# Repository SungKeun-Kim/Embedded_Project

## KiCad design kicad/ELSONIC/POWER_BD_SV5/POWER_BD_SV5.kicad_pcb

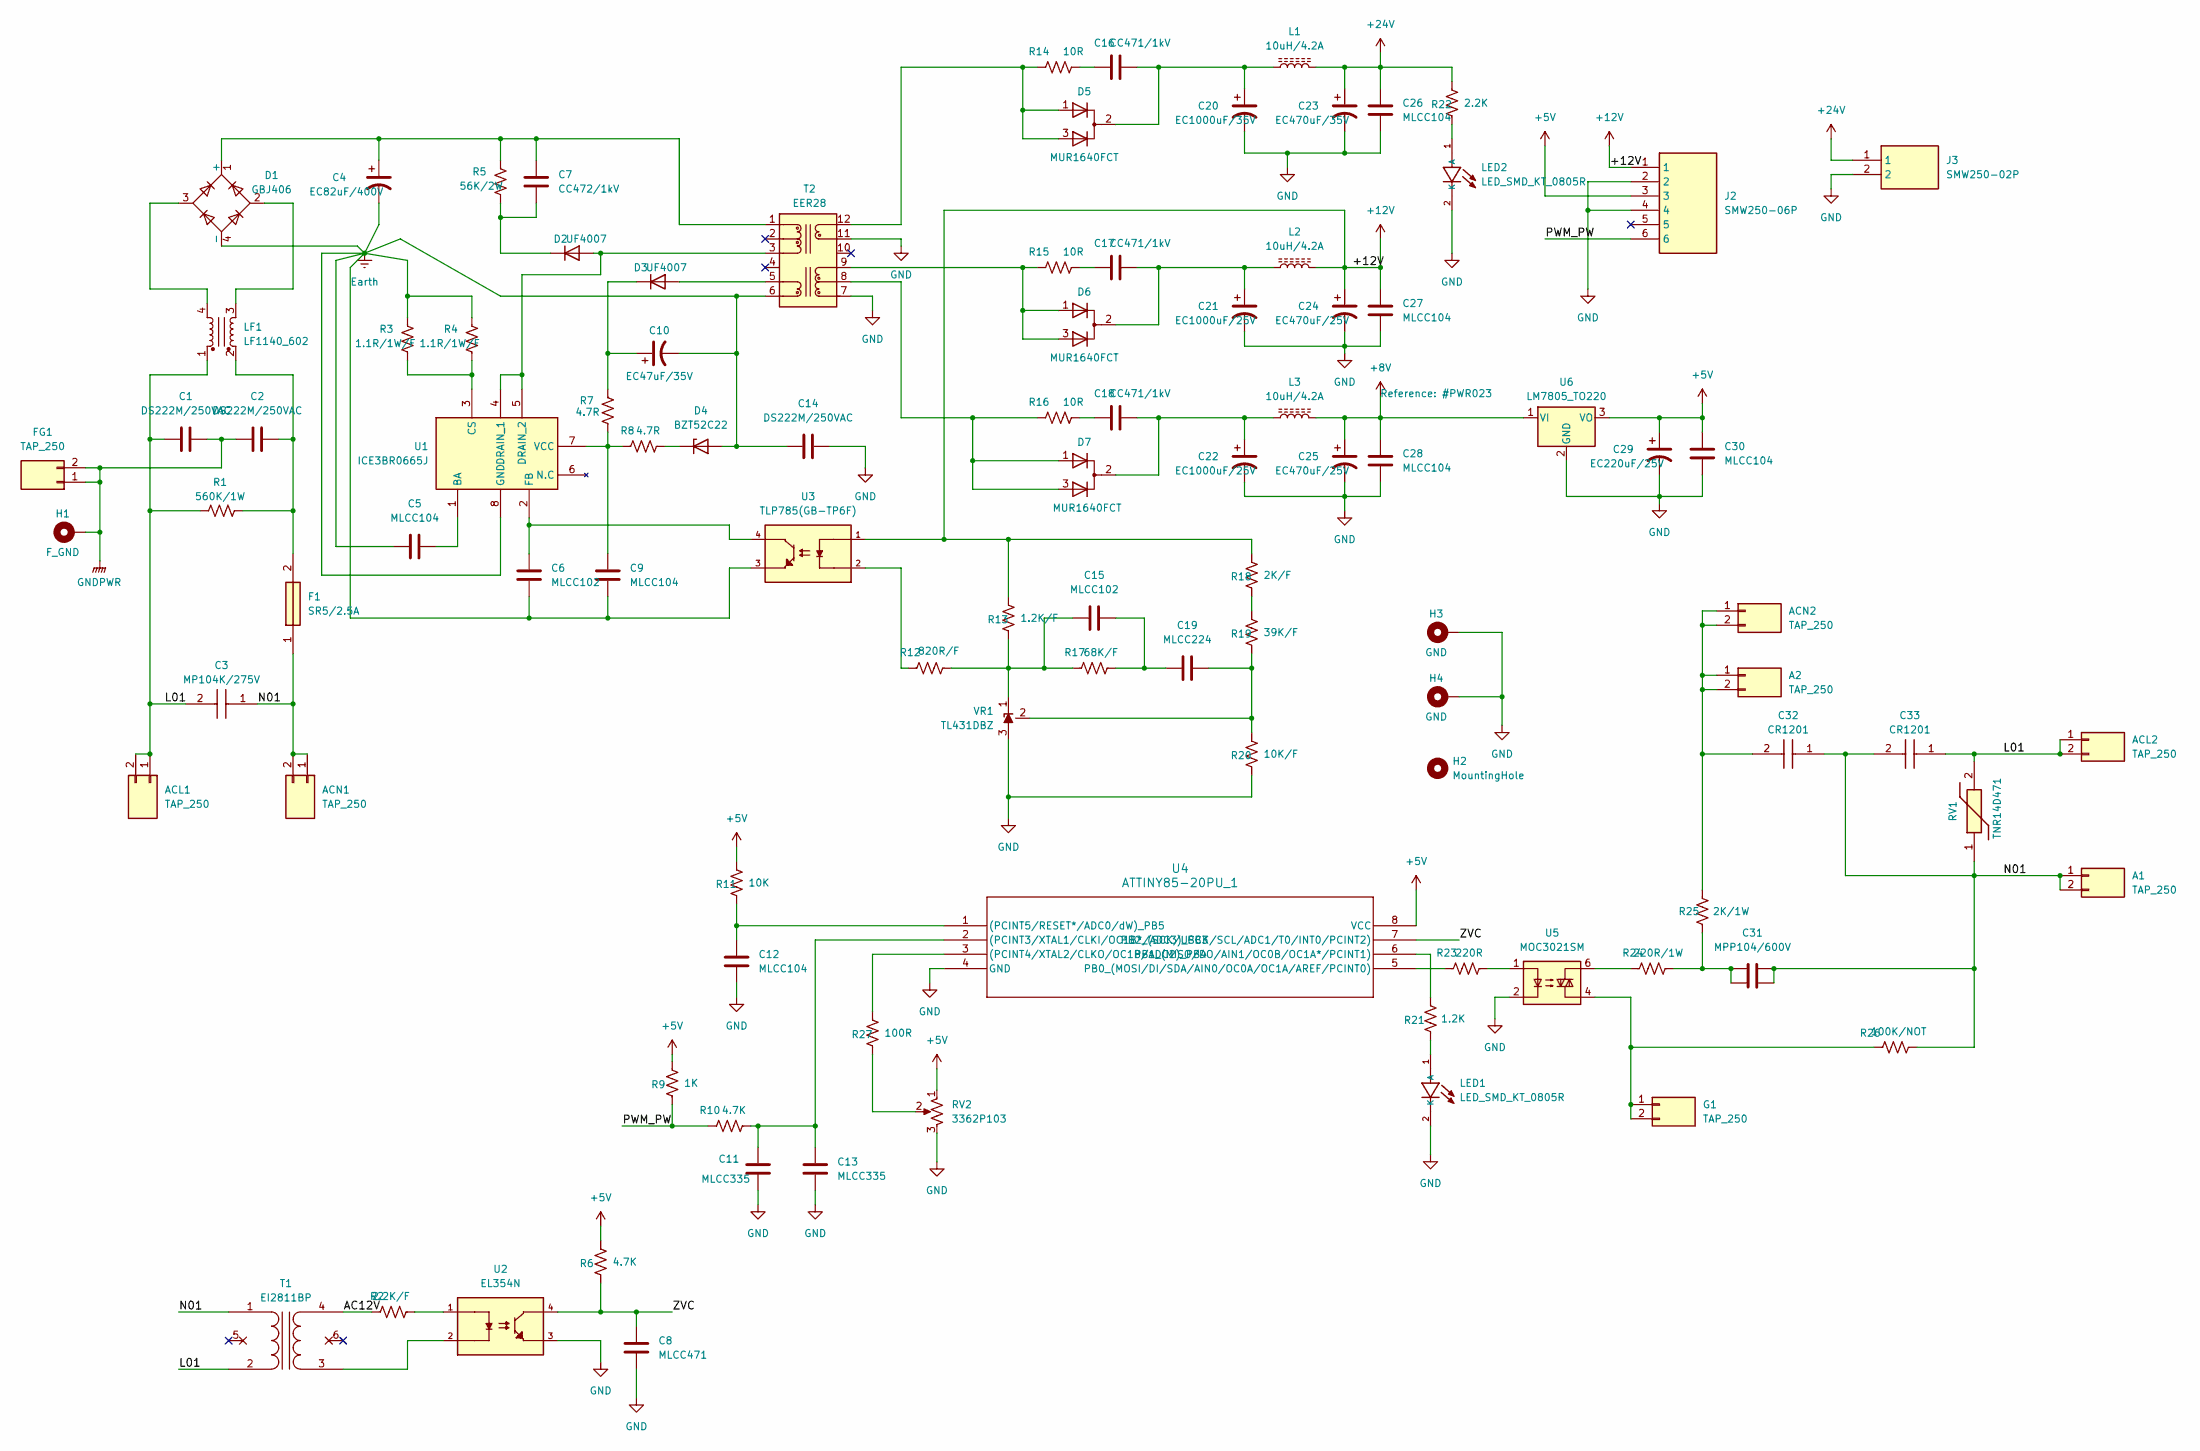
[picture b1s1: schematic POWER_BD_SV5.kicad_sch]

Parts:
A1, A2: TAP_250
ACL1, ACL2: TAP_250
ACN1, ACN2: TAP_250
C1, C2, C14: DS222M/250VAC; DS222M
C3: MP104K/275V; 104K_275V
C4: EC82uF/400V; 82uF_400V
C5, C9, C12, C26, C27, C28, C30: MLCC104; C_3216Metric; LCSC C1945
C6, C15: MLCC102; C_3216Metric; LCSC C1941
C7: CC472/1kV; C_3216Metric; LCSC C9192
C8: MLCC471; C_3216Metric; LCSC C1868
C10: EC47uF/35V; CP_Elec_6.3x5.4; LCSC C970678
C11, C13: MLCC335; C_3216Metric; LCSC C76663
C16, C17, C18: CC471/1kV; C_3216Metric; LCSC C9189
C19: MLCC224; C_3216Metric; LCSC C1857
C20: EC1000uF/35V; CP_Radial_D12.5mm_P5.00mm
C21, C22: EC1000uF/25V; CP_Radial_D10.0mm_P5.00mm
C23: EC470uF/35V; CP_Radial_D10.0mm_P5.00mm
C24, C25: EC470uF/25V; CP_Radial_D10.0mm_P5.00mm
C29: EC220uF/25V; CP_Elec_6.3x7.7; LCSC C2992606
C31: MPP104/600V; C_PP_P10.0mm_P21.2mm
C32, C33: CR1201; SPARK_KILLER
D1: GBJ406
D2, D3: UF4007; D_SMA; LCSC C81191
D4: BZT52C22; D_SOD-123; LCSC C2108
D5, D6, D7: MUR1640FCT; TO220AB_P2.55mm; LCSC C3011035
F1: SR5/2.5A; SR525ABK
FG1: TAP_250
G1: TAP_250
H1: F_GND; MTHole_3.5mm_7.5mmPad_GND
H2: MountingHole; MTHole_3.5mm
H3, H4: GND; MTHole_3.5mm_7.5mmPad_GND
J2: SMW250-06P; SMW250_06P
J3: SMW250-02P; SMW250_02P
L1, L2, L3: 10uH/4.2A; L_Sumida_CDMC6D28_7.25x6.5mm; LCSC C436542
LED1, LED2: LED_SMD_KT_0805R; LED_2012Metric; LCSC C2295
LF1: LF1140_602; LF1140
R1: 560K/1W; R_Axial_1W_P14.6mm
R2: 2.2K/F; R_3216Metric; LCSC C17948
R3, R4: 1.1R/1W/F; R_6332Metric; LCSC C5154651
R5: 56K/2W; R_Axial_2W_P20.32mm
R6, R10: 4.7K; R_3216Metric; LCSC C17936
R7, R8: 4.7R; R_3216Metric; LCSC C25385
R9: 1K; R_3216Metric; LCSC C17901
R11: 10K; R_3216Metric; LCSC C1489
R12: 820R/F; R_3216Metric; LCSC C17984
R13: 1.2K/F; R_3216Metric; LCSC C17891
R14, R15, R16: 10R; R_4532Metric; LCSC C2933875
R17: 68K/F; R_3216Metric; LCSC C25834
R18: 2K/F; R_3216Metric; LCSC C17944
R19: 39K/F; R_3216Metric; LCSC C18008
R20: 10K/F; R_3216Metric; LCSC C17902
R21: 1.2K; R_3216Metric; LCSC C26035
R22: 2.2K; R_3216Metric; LCSC C26038
R23: 220R; R_3216Metric; LCSC C17957
R24: 220R/1W; R_6332Metric; LCSC C38808
R25: 2K/1W; R_6332Metric; LCSC C37457
R26: 100K/NOT; R_Axial_0.25W_P10.16mm
R27: 100R; R_3216Metric; LCSC C25348
RV1: TNR14D471; TNR14D_P7.62
RV2: 3362P103; TRIM_3362P
T1: EI2811BP
T2: EER28; EER28_35_12P
U1: ICE3BR0665J; DIP-8_W7.62mm_Socket
U2: EL354N; SOIC-4_EL354_P2.54mm; LCSC C188348
U3: TLP785(GB-TP6F); SOP-4_7.5x4.1mm_P2.54mm; LCSC C45445
U4: ATTINY85-20PU_1; DIP-8_W7.62mm_Socket
U5: MOC3021SM; SOIC-6_P2.54mm; LCSC C115465
U6: LM7805_TO220; TO-252-2; LCSC C21706
VR1: TL431DBZ; SOT-23-3; LCSC C23892

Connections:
+5V: C29.1, C30.2, J2.3, R6.2, R9.2, R11.2, RV2.1, U4.8 (VCC), U6.3 (VO)
+8V: C25.1, C28.2, L3.2, U6.1 (VI)
+12V: C24.1, C27.2, J2.1, L2.2, R13.2, R18.2, U3.1
+24V: C23.1, C26.2, J3.1, L1.2, R22.2
/AC12V: R2.1, T1.4 (SB)
/L01: ACL1.1, ACL1.2, ACL2.1, ACL2.2, C1.1, C3.2, C33.1, LF1.1, R1.1, RV1.2, T1.2 (AB)
/N01: A1.1, A1.2, ACN1.1, ACN1.2, C3.1, C31.2, C31.4, C32.1, C33.2, F1.1, R26.2, RV1.1, T1.1 (AA)
/PWM_PW: J2.6, R9.1, R10.1
/ZVC: C8.2, R6.1, U2.4, U4.7 (PB2_(SCK/USCK/SCL/ADC1/T0/INT0/PCINT2))
Earth: C4.2, C5.1, C6.1, C9.1, C10.2, C14.1, D1.4 (-), D4.2 (A), R3.1, R4.1, T2.6 (Vcc_GND), U1.8 (GND), U3.3
GND: C8.1, C11.1, C12.1, C13.1, C14.2, C20.2, C21.2, C22.2, C23.2, C24.2, C25.2, C26.1, C27.1, C28.1, C29.2, C30.1, H3.1 (1_1), H4.1 (1_1), J2.2, J2.4, J3.2, LED1.2 (K), LED2.2 (K), R20.1, RV2.3, T2.7 (N_GND1), T2.11 (N_GND2), U2.3, U4.4 (GND), U5.2, U6.2 (GND), VR1.3 (A)
GNDPWR: C1.2, C2.1, FG1.1, FG1.2, H1.1 (1_1)
unnamed: A2.1, A2.2, ACN2.1, ACN2.2, C32.2, R25.1
unnamed: C2.2, F1.2, LF1.2, R1.2
unnamed: C15.2, C19.1, R17.2
unnamed: C16.1, R14.2
unnamed: C17.1, R15.2
unnamed: C18.1, R16.2
unnamed: C31.1, C31.3, R24.2, R25.2
unnamed: C4.1, C7.1, D1.1 (+), R5.1, T2.1 (P0)
unnamed: D1.2, LF1.3
unnamed: D1.3, LF1.4
unnamed: D2.2 (A), T2.3 (P2), U1.4 (DRAIN_1), U1.5 (DRAIN_2)
unnamed: C7.2, D2.1 (K), R5.2
unnamed: D3.2 (A), T2.5 (Vcc)
unnamed: C10.1, D3.1 (K), R7.1
unnamed: D4.1 (K), R8.2
unnamed: C16.2, C20.1, D5.2 (K), L1.1
unnamed: C17.2, C21.1, D6.2 (K), L2.1
unnamed: C18.2, C22.1, D7.2 (K), L3.1
unnamed: G1.1, G1.2, R26.1, U5.4
unnamed: LED1.1 (A), R21.2
unnamed: LED2.1 (A), R22.1
unnamed: R2.2, U2.1
unnamed: R12.1, U3.2
unnamed: R18.1, R19.2
unnamed: R23.2, U5.1
unnamed: R24.1, U5.6
unnamed: R27.1, RV2.2
unnamed: T1.3 (SA), U2.2
unnamed: D7.1 (A), D7.3 (A), R16.1, T2.8 (N1)
unnamed: D6.1 (A), D6.3 (A), R15.1, T2.9 (N2)
unnamed: D5.1 (A), D5.3 (A), R14.1, T2.12 (N3)
unnamed: C5.2, U1.1 (BA)
unnamed: R3.2, R4.2, U1.3 (CS)
unnamed: C6.2, U1.2 (FB), U3.4
unnamed: C9.2, R7.2, R8.1, U1.7 (VCC)
unnamed: C11.2, C13.2, R10.2, U4.2 ((PCINT3/XTAL1/CLKI/OC1B*/ADC3)_PB3)
unnamed: R27.2, U4.3 ((PCINT4/XTAL2/CLKO/OC1B/ADC2)_PB4)
unnamed: C12.2, R11.1, U4.1 ((PCINT5/RESET*/ADC0/dW)_PB5)
unnamed: R23.1, U4.5 (PB0_(MOSI/DI/SDA/AIN0/OC0A/OC1A/AREF/PC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)
unnamed: R21.1, U4.6 (PB1_(MISO/DO/AIN1/OC0B/OC1A*/PCINT1))
unnamed: C15.1, R12.2, R13.1, R17.1, VR1.1 (K)
unnamed: C19.2, R19.1, R20.2, VR1.2 (REF)

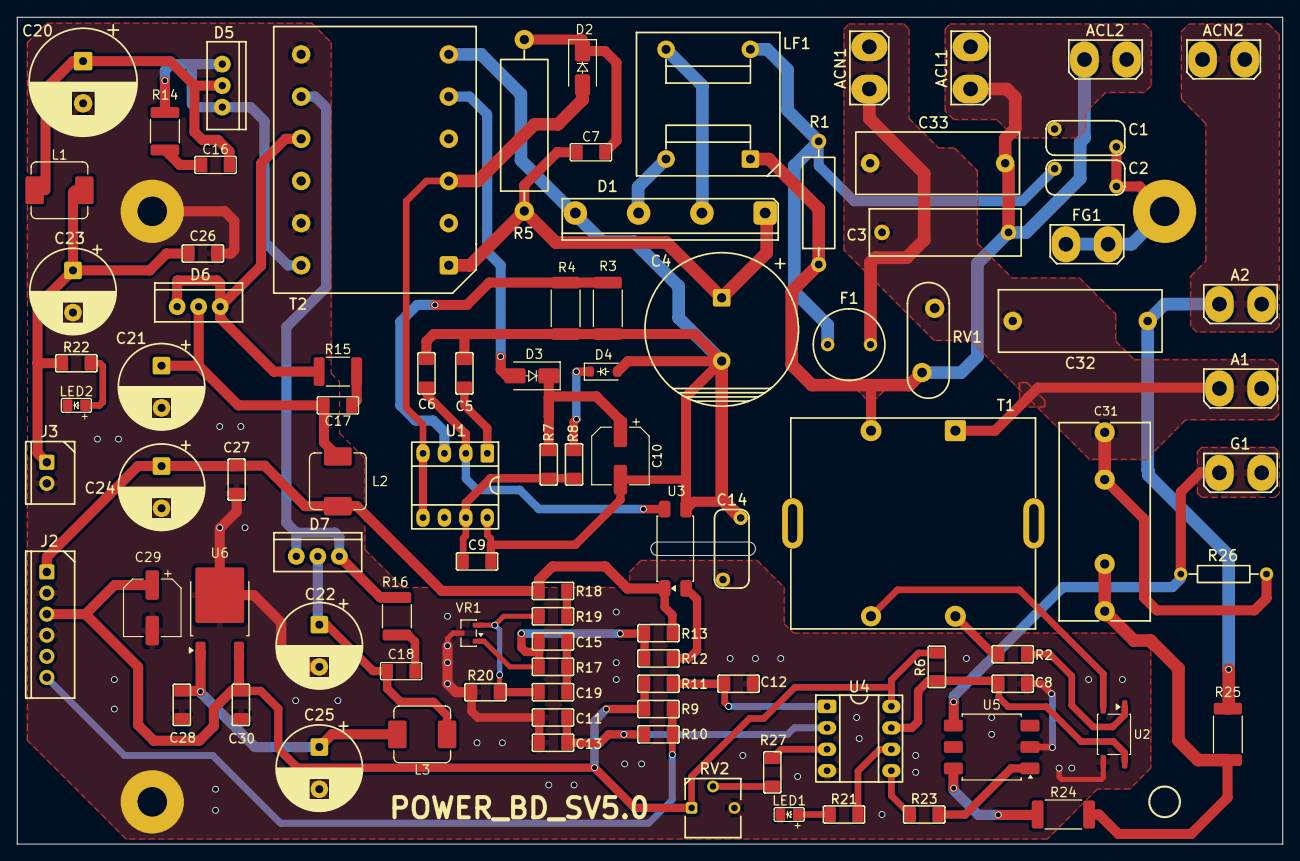
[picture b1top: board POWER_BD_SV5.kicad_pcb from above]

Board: 2 copper layers, 150.0 x 98.0 mm, 99 parts (0 on the bottom side), 54 nets.

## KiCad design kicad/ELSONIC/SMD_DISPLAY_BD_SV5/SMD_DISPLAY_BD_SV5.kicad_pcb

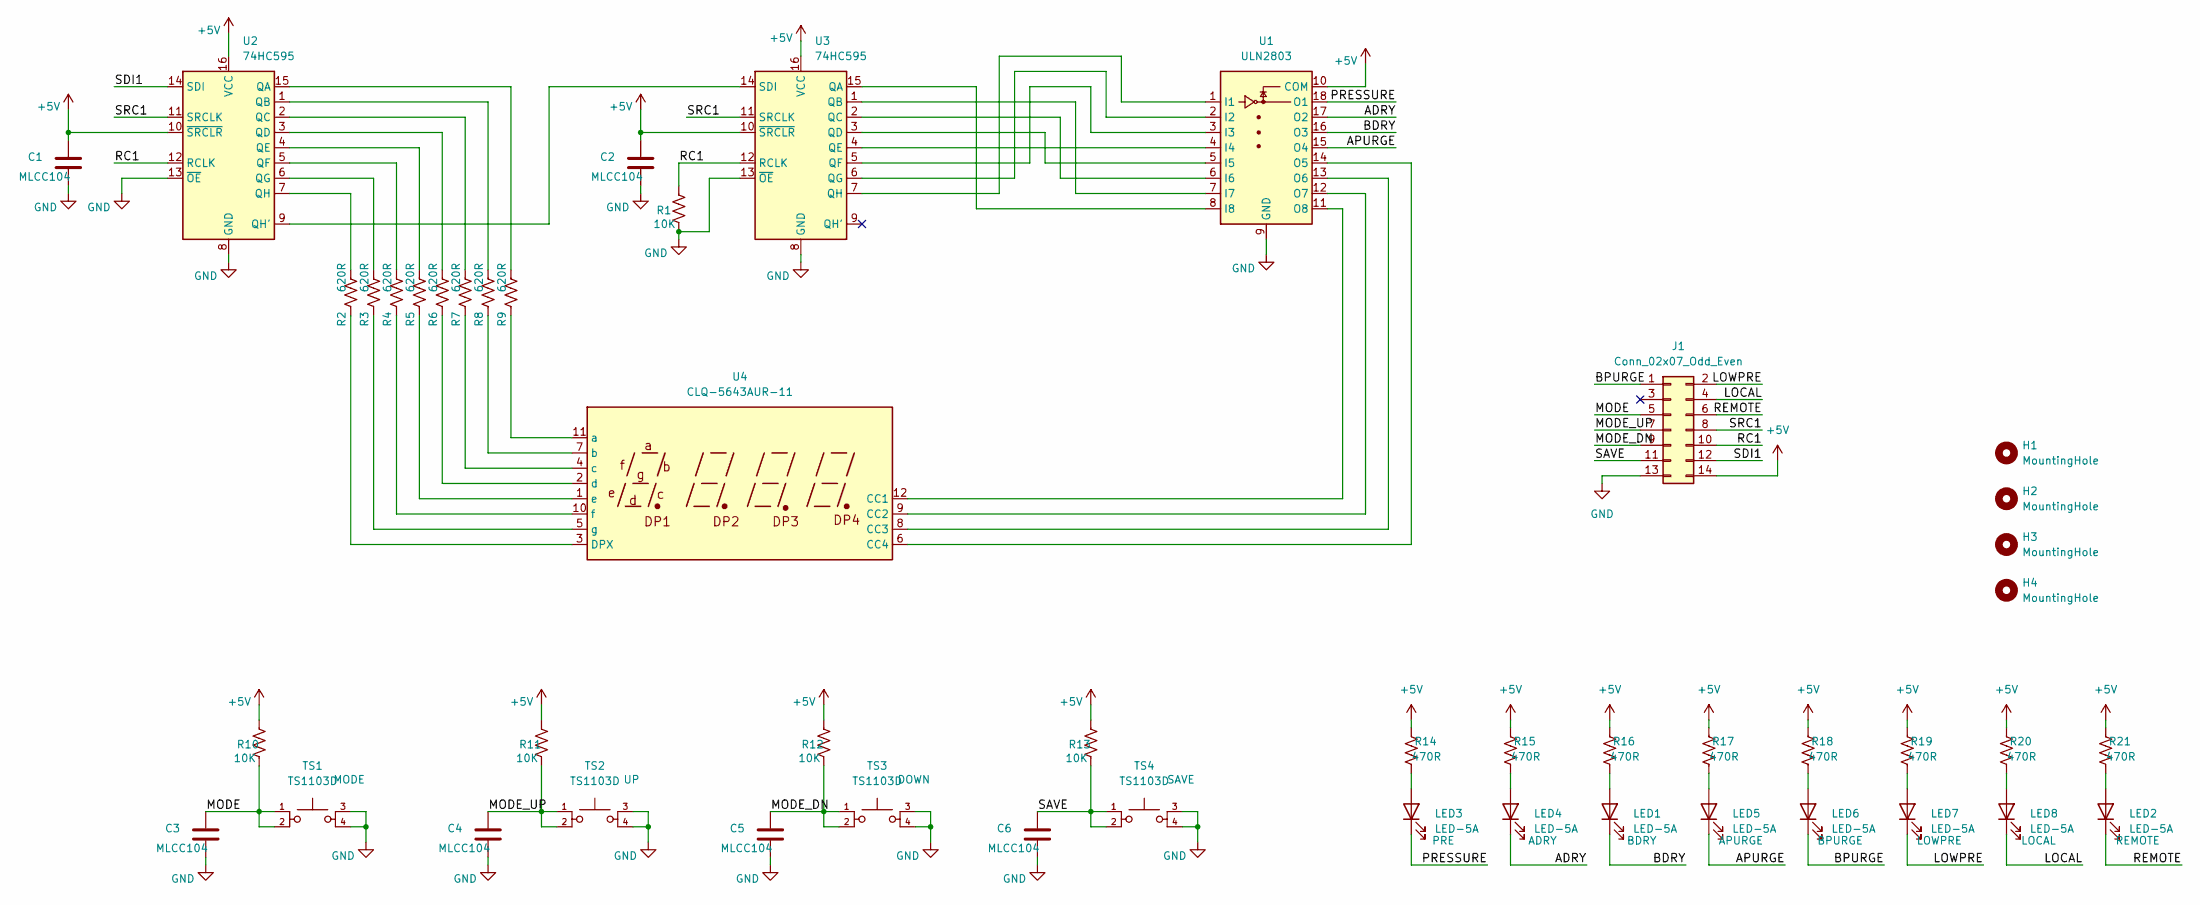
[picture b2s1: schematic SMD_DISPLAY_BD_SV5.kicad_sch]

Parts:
C1, C2, C3, C4, C5, C6: MLCC104; C_3216Metric; LCSC C1945
H1, H2, H3, H4: MountingHole; MTHole_3.5mm_ANTICOPPER
J1: Conn_02x07_Odd_Even; IDC-Header_2x07_P2.54mm_Vertical
LED1, LED2, LED3, LED4, LED5, LED6, LED7, LED8: LED-5A; LED_D5.0mm
R1, R10, R11, R12, R13: 10K; R_3216Metric; LCSC C136460
R2, R3, R4, R5, R6, R7, R8, R9: 620R; R_3216Metric; LCSC C966344
R14, R15, R16, R17, R18, R19, R20, R21: 470R; R_3216Metric; LCSC C114948
TS1, TS2, TS3, TS4: TS1103D; SW_PUSH-12mm
U1: ULN2803; SOP-18_7.495x11.515mm_P1.27mm; LCSC C18164409
U2, U3: 74HC595; SOIC-16_3.9x9.9mm_P1.27mm; LCSC C5947
U4: CLQ-5643AUR-11

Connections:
+5V: C1.2, C2.2, J1.14, R10.2, R11.2, R12.2, R13.2, R14.2, R15.2, R16.2, R17.2, R18.2, R19.2, R20.2, R21.2, U1.10 (COM), U2.10 (~SRCLR), U2.16 (VCC), U3.10 (~SRCLR), U3.16 (VCC)
/ADRY: LED4.1 (K), U1.17 (O2)
/APURGE: LED5.1 (K), U1.15 (O4)
/BDRY: LED1.1 (K), U1.16 (O3)
/BPURGE: J1.1, LED6.1 (K)
/LOCAL: J1.4, LED8.1 (K)
/LOWPRE: J1.2, LED7.1 (K)
/MODE: C3.2, J1.5, R10.1, TS1.1, TS1.2
/MODE_DN: C5.2, J1.9, R12.1, TS3.1, TS3.2
/MODE_UP: C4.2, J1.7, R11.1, TS2.1, TS2.2
/PRESSURE: LED3.1 (K), U1.18 (O1)
/RC1: J1.10, R1.2, U2.12 (RCLK), U3.12 (RCLK)
/REMOTE: J1.6, LED2.1 (K)
/SAVE: C6.2, J1.11, R13.1, TS4.1, TS4.2
/SDI1: J1.12, U2.14 (SDI)
/SRC1: J1.8, U2.11 (SRCLK), U3.11 (SRCLK)
GND: C1.1, C2.1, C3.1, C4.1, C5.1, C6.1, J1.13, R1.1, TS1.3, TS1.4, TS2.3, TS2.4, TS3.3, TS3.4, TS4.3, TS4.4, U1.9 (GND), U2.8 (GND), U2.13 (~OE), U3.8 (GND), U3.13 (~OE)
unnamed: LED1.2 (A), R16.1
unnamed: LED2.2 (A), R21.1
unnamed: LED3.2 (A), R14.1
unnamed: LED4.2 (A), R15.1
unnamed: LED5.2 (A), R17.1
unnamed: LED6.2 (A), R18.1
unnamed: LED7.2 (A), R19.1
unnamed: LED8.2 (A), R20.1
unnamed: U1.1 (I1), U3.7 (QH)
unnamed: U1.2 (I2), U3.6 (QG)
unnamed: U1.3 (I3), U3.5 (QF)
unnamed: U1.4 (I4), U3.4 (QE)
unnamed: U1.5 (I5), U3.3 (QD)
unnamed: U1.6 (I6), U3.2 (QC)
unnamed: U1.7 (I7), U3.1 (QB)
unnamed: U1.8 (I8), U3.15 (QA)
unnamed: U1.14 (O5), U4.6 (CC4)
unnamed: U1.13 (O6), U4.8 (CC3)
unnamed: U1.12 (O7), U4.9 (CC2)
unnamed: U1.11 (O8), U4.12 (CC1)
unnamed: R9.2, U2.15 (QA)
unnamed: R8.2, U2.1 (QB)
unnamed: R7.2, U2.2 (QC)
unnamed: R6.2, U2.3 (QD)
unnamed: R5.2, U2.4 (QE)
unnamed: R4.2, U2.5 (QF)
unnamed: R3.2, U2.6 (QG)
unnamed: U2.9 (QH'), U3.14 (SDI)
unnamed: R2.2, U2.7 (QH)
unnamed: R2.1, U4.3 (DPX)
unnamed: R9.1, U4.11 (a)
unnamed: R8.1, U4.7 (b)
unnamed: R7.1, U4.4 (c)
unnamed: R6.1, U4.2 (d)
unnamed: R5.1, U4.1 (e)
unnamed: R4.1, U4.10 (f)
unnamed: R3.1, U4.5 (g)

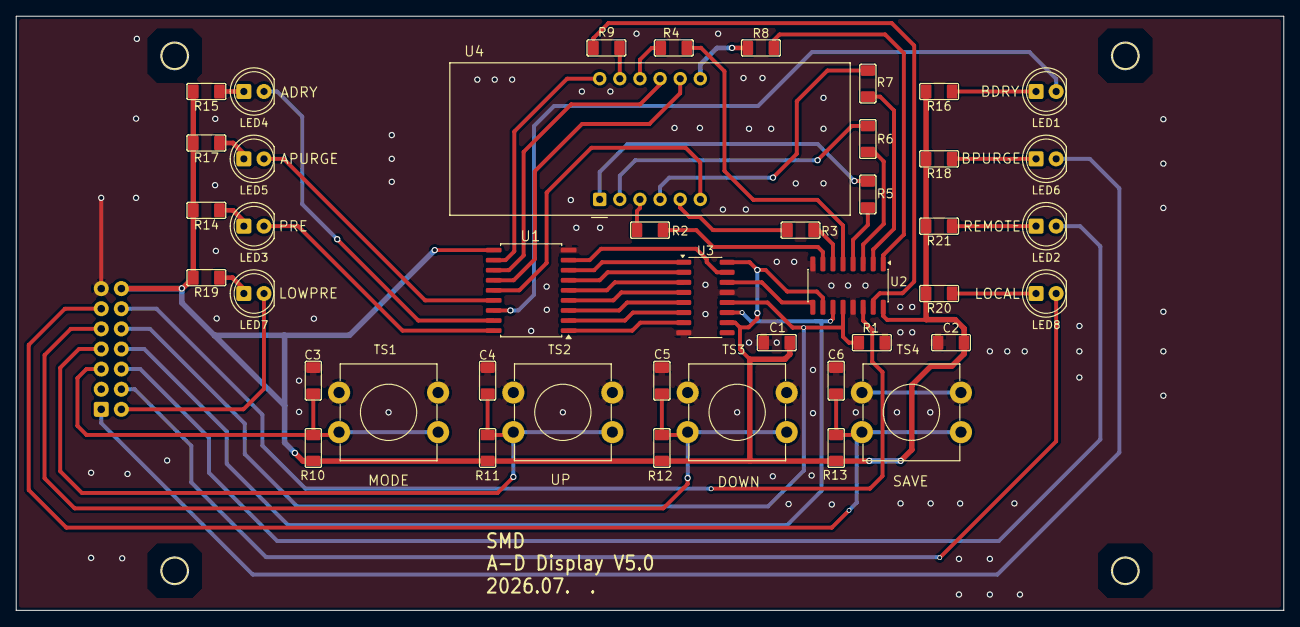
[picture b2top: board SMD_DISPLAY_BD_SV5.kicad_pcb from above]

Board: 2 copper layers, 160.0 x 75.0 mm, 48 parts (1 on the bottom side), 54 nets.

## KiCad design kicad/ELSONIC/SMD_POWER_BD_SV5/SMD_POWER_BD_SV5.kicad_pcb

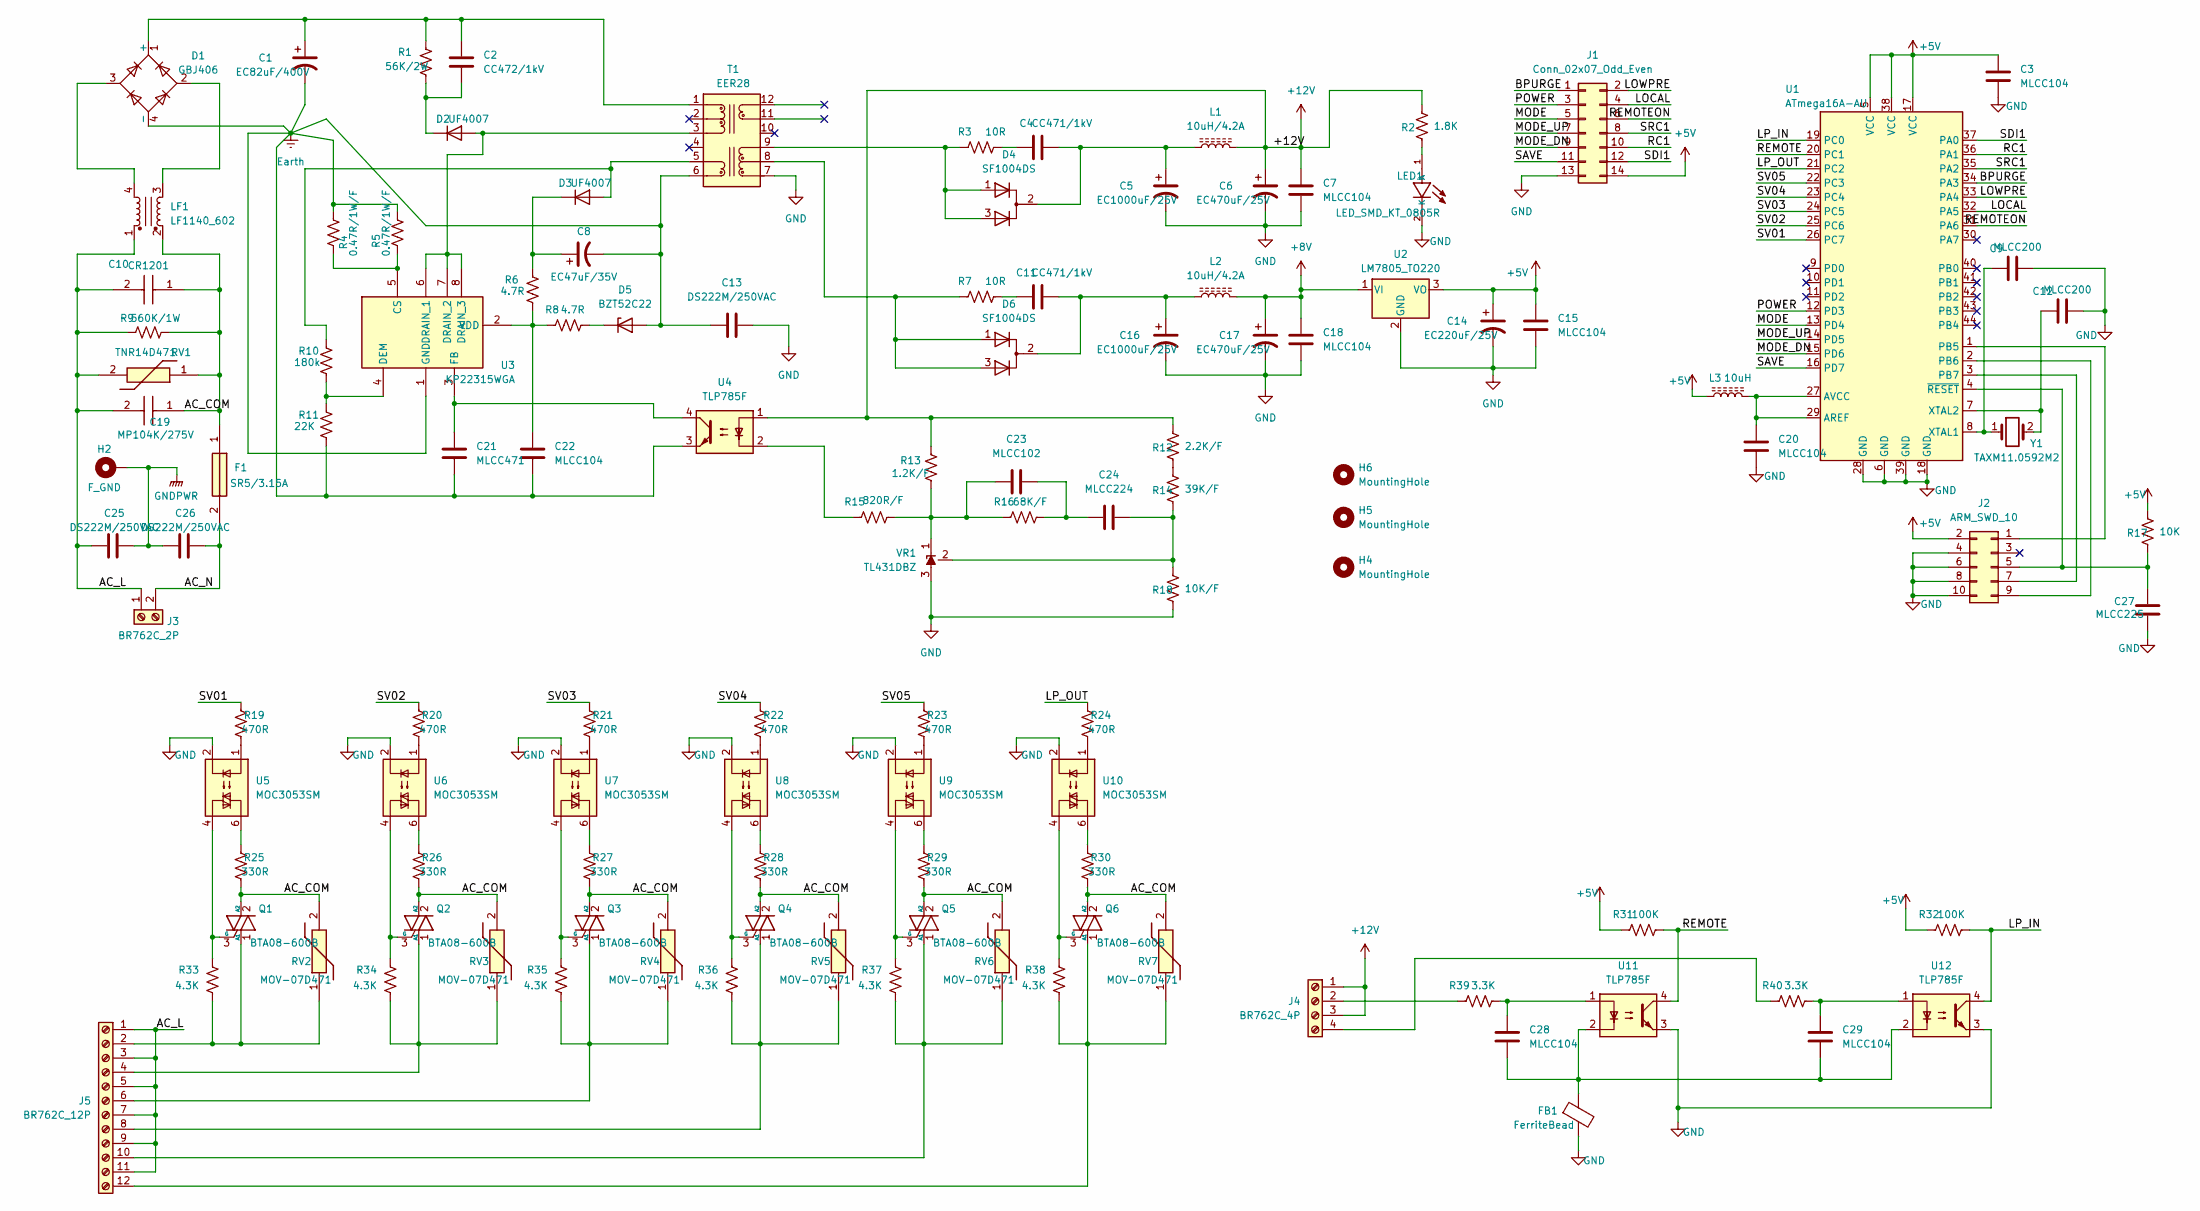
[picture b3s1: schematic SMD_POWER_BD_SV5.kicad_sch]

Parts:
C1: EC82uF/400V; 82uF_400V
C2: CC472/1kV; C_3216Metric; LCSC C9192
C3, C7, C15, C18, C20, C22, C28, C29: MLCC104; C_3216Metric; LCSC C24497
C4, C11: CC471/1kV; C_3216Metric; LCSC C9189
C5, C16: EC1000uF/25V; CP_Radial_D10.0mm_P5.00mm
C6, C17: EC470uF/25V; CP_Radial_D10.0mm_P5.00mm
C8: EC47uF/35V; CP_Elec_6.3x5.4; LCSC C970678
C9, C12: MLCC200; C_3216Metric; LCSC C377026
C10: CR1201; SPARK_KILLER
C13, C25, C26: DS222M/250VAC; DS222M
C14: EC220uF/25V; CP_Elec_6.3x7.7; LCSC C2992606
C19: MP104K/275V; 104K_275V
C21: MLCC471; C_3216Metric; LCSC C106069
C23: MLCC102; C_3216Metric; LCSC C1941
C24: MLCC224; C_3216Metric; LCSC C1857
C27: MLCC225; C_3216Metric; LCSC C107183
D1: GBJ406
D2, D3: UF4007; D_SMA; LCSC C81191
D4, D6: SF1004DS; TO-252-2; LCSC C3011035
D5: BZT52C22; D_SOD-123; LCSC C2108
F1: SR5/3.15A; SR525ABK
FB1: FerriteBead; R_Axial_0.25W_P10.16mm
H2: F_GND; MTHole_3.5mm_7.5mmPad_GND
H4, H6: MountingHole; MTHole_3.5mm
H5: MountingHole; MTHole_3.5mm_ANTICOPPER
J1: Conn_02x07_Odd_Even; IDC-Header_2x07_P2.54mm_Vertical
J2: ARM_SWD_10; IDC-Header_2x05_P2.54mm_Vertical
J3: BR762C_2P; BR762_02P
J4: BR762C_4P; BR762_04P
J5: BR762C_12P; BR762_12P
L1, L2: 10uH/4.2A; L_Sumida_CDMC6D28_7.25x6.5mm; LCSC C436542
L3: 10uH; R_3216Metric; LCSC C412018
LED1: LED_SMD_KT_0805R; LED_2012Metric; LCSC C2295
LF1: LF1140_602; LF1140
Q1, Q2, Q3, Q4, Q5, Q6: BTA08-600B; TO-220-3_Vertical
R1: 56K/2W; R_Axial_2W_P20.32mm
R2: 1.8K; R_3216Metric; LCSC C102291
R3, R7: 10R; R_4532Metric; LCSC C2933875
R4, R5: 0.47R/1W/F; R_6332Metric; LCSC C21097
R6, R8: 4.7R; R_3216Metric; LCSC C104836
R9: 560K/1W; R_Axial_1W_P14.6mm
R10: 180k; R_3216Metric; LCSC C137381
R11: 22K; R_3216Metric; LCSC C140036
R12: 2.2K/F; R_3216Metric; LCSC C140044
R13: 1.2K/F; R_3216Metric; LCSC C104614
R14: 39K/F; R_3216Metric; LCSC C18008
R15: 820R/F; R_3216Metric; LCSC C17984
R16: 68K/F; R_3216Metric; LCSC C137239
R17: 10K; R_3216Metric; LCSC C136460
R18: 10K/F; R_3216Metric; LCSC C17902
R19, R20, R21, R22, R23, R24: 470R; R_3216Metric; LCSC C104820
R25, R26, R27, R28, R29, R30: 330R; R_3216Metric; LCSC C414913
R31, R32: 100K; R_3216Metric; LCSC C127274
R33, R34, R35, R36, R37, R38: 4.3K; R_3216Metric; LCSC C2759585
R39, R40: 3.3K; R_3216Metric; LCSC C168540
RV1: TNR14D471; TNR14D_P7.62
RV2, RV3, RV4, RV5, RV6, RV7: MOV-07D471; C_Disc_D8.0mm_W4.8mm_P5.00mm
T1: EER28; EER28_35_12P
U1: ATmega16A-AU; TQFP-44_10x10mm_P0.8mm; LCSC C5658
U2: LM7805_TO220; TO-252-2; LCSC C21706
U3: KP22315WGA; ASOP-6_L6.2xW3.9_P1.27mm; LCSC C2848206
U4, U11, U12: TLP785F; SOP-4_7.5x4.1mm_P2.54mm; LCSC C45445
U5, U6, U7, U8, U9, U10: MOC3053SM; SOIC-6_P2.54mm-CUTLINE; LCSC C22469445
VR1: TL431DBZ; SOT-23-3; LCSC C23892
Y1: TAXM11.0592M2; Crystal_SMD_HC49-SD; LCSC C362349

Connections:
+5V: C3.2, C14.1, C15.2, J1.14, J2.2, L3.1, R17.2, R31.1, R32.1, U1.5 (VCC), U1.17 (VCC), U1.38 (VCC), U2.3 (VO)
+8V: C17.1, C18.2, L2.2, U2.1 (VI)
+12V: C6.1, C7.2, J4.1, J4.3, L1.2, R2.2, R12.2, R13.2, U4.1
/AC_COM: C10.1, C19.1, F1.1, LF1.2, Q1.2 (A2), Q2.2 (A2), Q3.2 (A2), Q4.2 (A2), Q5.2 (A2), Q6.2 (A2), R9.2, R25.1, R26.1, R27.1, R28.1, R29.1, R30.1, RV1.1, RV2.2, RV3.2, RV4.2, RV5.2, RV6.2, RV7.2
/AC_L: C10.2, C19.2, C25.1, J3.1, J5.1, J5.3, J5.5, J5.7, J5.9, J5.11, LF1.1, R9.1, RV1.2
/AC_N: C26.2, F1.2, J3.2
/BPURGE: J1.1, U1.34 (PA3)
/LOCAL: J1.4, U1.32 (PA5)
/LOWPRE: J1.2, U1.33 (PA4)
/LP_IN: R32.2, U1.19 (PC0), U12.4
/LP_OUT: R24.2, U1.21 (PC2)
/MODE: J1.5, U1.13 (PD4)
/MODE_DN: J1.9, U1.15 (PD6)
/MODE_UP: J1.7, U1.14 (PD5)
/POWER: J1.3, U1.12 (PD3)
/RC1: J1.10, U1.36 (PA1)
/REMOTE: R31.2, U1.20 (PC1), U11.4
/REMOTEON: J1.6, U1.31 (PA6)
/SAVE: J1.11, U1.16 (PD7)
/SDI1: J1.12, U1.37 (PA0)
/SRC1: J1.8, U1.35 (PA2)
/SV01: R19.2, U1.26 (PC7)
/SV02: R20.2, U1.25 (PC6)
/SV03: R21.2, U1.24 (PC5)
/SV04: R22.2, U1.23 (PC4)
/SV05: R23.2, U1.22 (PC3)
Earth: C1.2, C8.2, C13.1, C21.1, C22.1, D1.4 (-), D5.2 (A), R4.1, R5.1, R11.2, T1.6 (Vcc_GND), U3.1 (GND), U4.3
GND: C3.1, C5.2, C6.2, C7.1, C9.2, C12.2, C13.2, C14.2, C15.1, C16.2, C17.2, C18.1, C20.1, C27.1, FB1.2, J1.13, J2.4, J2.6, J2.8, J2.10, LED1.2 (K), R18.1, T1.7 (N_GND1), U1.6 (GND), U1.18 (GND), U1.28 (GND), U1.39 (GND), U2.2 (GND), U5.2, U6.2, U7.2, U8.2, U9.2, U10.2, U11.3, U12.3, VR1.3 (A)
GNDPWR: C25.2, C26.1, H2.1 (1_1)
unnamed: C4.1, R3.2
unnamed: C11.1, R7.2
unnamed: C23.2, C24.1, R16.2
unnamed: C28.1, C29.1, FB1.1, U11.2, U12.2
unnamed: C28.2, R39.2, U11.1
unnamed: C29.2, R40.2, U12.1
unnamed: C1.1, C2.1, D1.1 (+), R1.1, T1.1 (P0)
unnamed: D1.2, LF1.3
unnamed: D1.3, LF1.4
unnamed: D2.2 (A), T1.3 (P2), U3.6 (DRAIN_1), U3.7 (DRAIN_2), U3.8 (DRAIN_3)
unnamed: C2.2, D2.1 (K), R1.2
unnamed: D3.2 (A), R10.1, T1.5 (Vcc)
unnamed: C8.1, D3.1 (K), R6.1
unnamed: C4.2, C5.1, D4.2 (K), L1.1
unnamed: D5.1 (K), R8.2
unnamed: C11.2, C16.1, D6.2 (K), L2.1
unnamed: J2.1, U1.1 (PB5)
unnamed: C27.2, J2.5, R17.1, U1.4 (~RESET)
unnamed: J2.7, U1.3 (PB7)
unnamed: J2.9, U1.2 (PB6)
unnamed: J4.2, R39.1
unnamed: J4.4, R40.1
unnamed: J5.2, Q1.1 (A1), R33.1, RV2.1
unnamed: J5.4, Q2.1 (A1), R34.1, RV3.1
unnamed: J5.6, Q3.1 (A1), R35.1, RV4.1
unnamed: J5.8, Q4.1 (A1), R36.1, RV5.1
unnamed: J5.10, Q5.1 (A1), R37.1, RV6.1
unnamed: J5.12, Q6.1 (A1), R38.1, RV7.1
unnamed: LED1.1 (A), R2.1
unnamed: Q1.3 (G), R33.2, U5.4
unnamed: Q2.3 (G), R34.2, U6.4
unnamed: Q3.3 (G), R35.2, U7.4
unnamed: Q4.3 (G), R36.2, U8.4
unnamed: Q5.3 (G), R37.2, U9.4
unnamed: Q6.3 (G), R38.2, U10.4
unnamed: R12.1, R14.2
unnamed: R15.1, U4.2
unnamed: R19.1, U5.1
unnamed: R20.1, U6.1
unnamed: R21.1, U7.1
unnamed: R22.1, U8.1
unnamed: R23.1, U9.1
unnamed: R24.1, U10.1
unnamed: R25.2, U5.6
unnamed: R26.2, U6.6
unnamed: R27.2, U7.6
unnamed: R28.2, U8.6
unnamed: R29.2, U9.6
unnamed: R30.2, U10.6
unnamed: D6.1 (A), D6.3 (A), R7.1, T1.8 (N1)
unnamed: D4.1 (A), D4.3 (A), R3.1, T1.9 (N2)
unnamed: C20.2, L3.2, U1.27 (AVCC), U1.29 (AREF)
unnamed: C9.1, U1.8 (XTAL1), Y1.1
unnamed: C12.1, U1.7 (XTAL2), Y1.2
unnamed: R4.2, R5.2, U3.5 (CS)
unnamed: R10.2, R11.1, U3.4 (DEM)
unnamed: C21.2, U3.3 (FB), U4.4
unnamed: C22.2, R6.2, R8.1, U3.2 (VDD)
unnamed: C23.1, R13.1, R15.2, R16.1, VR1.1 (K)
unnamed: C24.2, R14.1, R18.2, VR1.2 (REF)

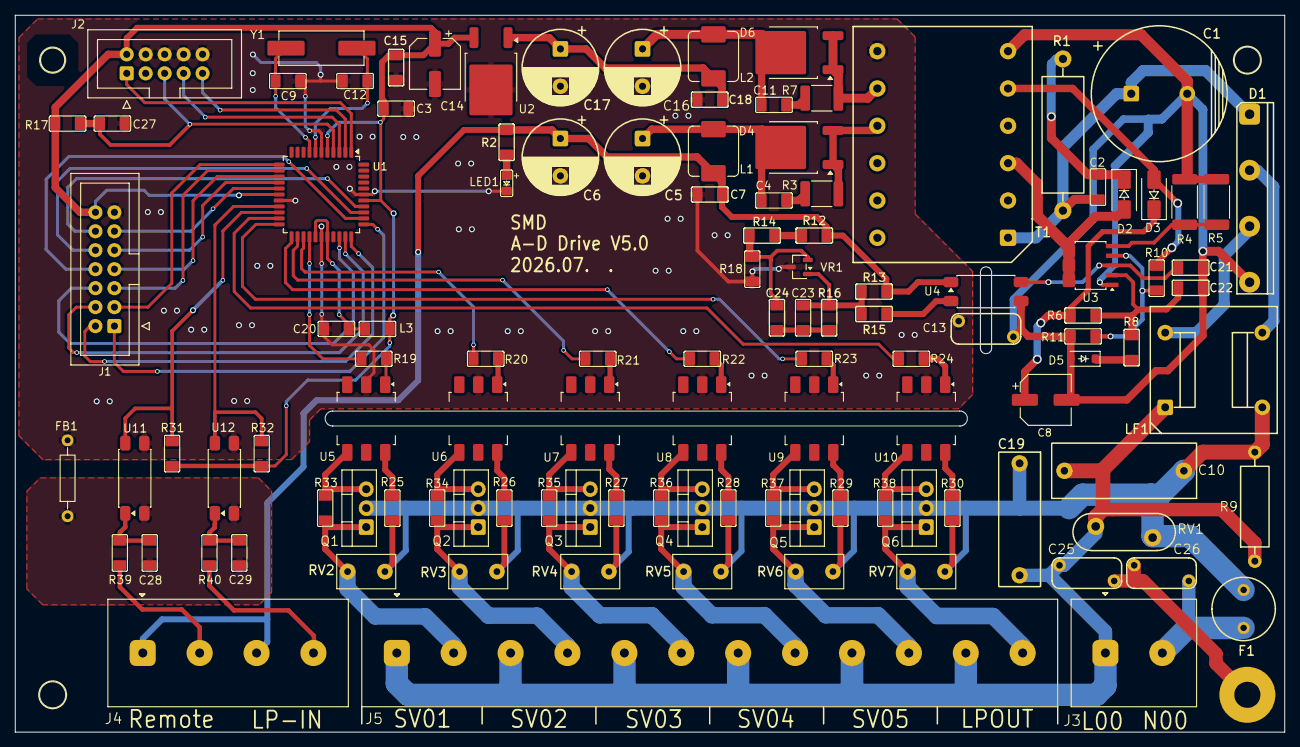
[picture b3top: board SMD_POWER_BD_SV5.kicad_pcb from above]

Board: 2 copper layers, 170.0 x 96.0 mm, 119 parts (0 on the bottom side), 89 nets.

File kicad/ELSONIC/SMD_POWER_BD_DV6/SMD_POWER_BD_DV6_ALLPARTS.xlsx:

| Value | Reference | Footprint | LCSC
1 | MOC3053SM | U5,U6,U7,U8,U9,U10 | 01_MyFoot_ICs:SOIC-6_P2.54mm-CUTLINE | C22469445
2 | 1.1R/1W/F | R4,R5 | 04_MyFoot_Passive:R_6332Metric | C5154651
3 | SF1004DS | D4,D6 | 01_MyFoot_ICs:TO-252-2 | C3011035
4 | EC220uF/25V | C14 | 04_MyFoot_Passive:CP_Elec_6.3x7.7 | C2992606
5 | 10R | R3,R7 | 04_MyFoot_Passive:R_4532Metric | C2933875
6 | 4.3K | R33,R34,R35,R36,R37,R38 | 04_MyFoot_Passive:R_3216Metric | C2759585
7 | EC47uF/35V | C8 | 04_MyFoot_Passive:CP_Elec_6.3x5.4 | C970678
8 | 10uH/4.2A | L1,L2 | 04_MyFoot_Passive:L_Sumida_CDMC6D28_7.25x6.5mm | C436542
9 | 330R | R25,R26,R27,R28,R29,R30 | 04_MyFoot_Passive:R_3216Metric | C414913
10 | 10uH | L3 | 04_MyFoot_Passive:R_3216Metric | C412018
11 | MLCC200 | C9,C12 | 04_MyFoot_Passive:C_3216Metric | C377026
12 | TAXM11.0592M2 | Y1 | 03_MyFoot_Active:Crystal_SMD_HC49-SD | C362349
13 | 3.3K | R39,R40 | 04_MyFoot_Passive:R_3216Metric | C168540
14 | 2.2K/F | R12 | 04_MyFoot_Passive:R_3216Metric | C140044
15 | 68K/F | R16 | 04_MyFoot_Passive:R_3216Metric | C137239
16 | 10K | R17 | 04_MyFoot_Passive:R_3216Metric | C136460
17 | 100K | R31,R32 | 04_MyFoot_Passive:R_3216Metric | C127274
18 | MLCC225 | C27 | 04_MyFoot_Passive:C_3216Metric | C107183
19 | 4.7R | R6,R8 | 04_MyFoot_Passive:R_3216Metric | C104836
20 | 470R | R19,R20,R21,R22,R23,R24 | 04_MyFoot_Passive:R_3216Metric | C104820
21 | 1.2K/F | R13 | 04_MyFoot_Passive:R_3216Metric | C104614
22 | 1.8K | R2 | 04_MyFoot_Passive:R_3216Metric | C102291
23 | UF4007 | D2,D3 | 03_MyFoot_Active:D_SMA | C81191
24 | TLP785F | U4,U11,U12 | 01_MyFoot_ICs:SOP-4_7.5x4.1mm_P2.54mm | C45445
25 | MLCC104 | C3,C7,C15,C18,C20,C22,C28,C29,C30 | 04_MyFoot_Passive:C_3216Metric | C24497
26 | TL431DBZ | VR1 | 01_MyFoot_ICs:SOT-23-3 | C23892
27 | LM7805_TO220 | U2 | 01_MyFoot_ICs:TO-252-2 | C21706
28 | 39K/F | R14 | 04_MyFoot_Passive:R_3216Metric | C18008
29 | 820R/F | R15 | 04_MyFoot_Passive:R_3216Metric | C17984
30 | 10K/F | R18 | 04_MyFoot_Passive:R_3216Metric | C17902
31 | CC472/1kV | C2 | 04_MyFoot_Passive:C_3216Metric | C9192
32 | CC471/1kV | C4,C11 | 04_MyFoot_Passive:C_3216Metric | C9189
33 | ATmega16A-AU | U1 | 00_MyFoot_MCU:TQFP-44_10x10mm_P0.8mm | C5658
34 | LED_SMD_KT_0805R | LED1 | 03_MyFoot_Active:LED_2012Metric | C2295
35 | BZT52C22 | D5 | 03_MyFoot_Active:D_SOD-123 | C2108
36 | MLCC102 | C21,C23 | 04_MyFoot_Passive:C_3216Metric | C1941
37 | MLCC224 | C24 | 04_MyFoot_Passive:C_3216Metric | C1857
38 | ICE3BR0665J | U13 | 01_MyFoot_ICs:DIP-8_W7.62mm_Socket
39 | EER28 | T1 | 04_MyFoot_Passive:EER28_35_12P
40 | MOV-07D471 | RV2,RV3,RV4,RV5,RV6,RV7 | 04_MyFoot_Passive:C_Disc_D8.0mm_W4.8mm_P5.00mm
41 | TNR14D471 | RV1 | 04_MyFoot_Passive:TNR14D_P7.62
42 | 560K/1W | R9 | 04_MyFoot_Passive:R_Axial_1W_P14.6mm
43 | 56K/2W | R1 | 04_MyFoot_Passive:R_Axial_2W_P20.32mm
44 | BTA08-600B | Q1,Q2,Q3,Q4,Q5,Q6 | 03_MyFoot_Active:TO-220-3_Vertical
45 | LF1140_602 | LF1 | 04_MyFoot_Passive:LF1140
46 | BR762C_12P | J5 | 02_MyFoot_Connectors:BR762_12P
47 | BR762C_4P | J4 | 02_MyFoot_Connectors:BR762_04P
48 | BR762C_2P | J3 | 02_MyFoot_Connectors:BR762_02P
49 | AVR_SPI_10 | J2 | 02_MyFoot_Connectors:IDC-Header_2x05_P2.54mm_Vertical
50 | Conn_02x07_Odd_Even | J1 | 02_MyFoot_Connectors:IDC-Header_2x07_P2.54mm_Vertical
51 | FerriteBead | FB1 | 04_MyFoot_Passive:R_Axial_0.25W_P10.16mm
52 | SR5/3.15A | F1 | 05_MyFoot_Others:SR525ABK
53 | GBJ406 | D1 | 03_MyFoot_Active:GBJ406
54 | MP104K/275V | C19 | 04_MyFoot_Passive:104K_275V
55 | DS222M/250VAC | C13,C25,C26 | 04_MyFoot_Passive:DS222M
56 | CR1201 | C10 | 04_MyFoot_Passive:SPARK_KILLER
57 | EC470uF/25V | C6,C17 | 04_MyFoot_Passive:CP_Radial_D10.0mm_P5.00mm
58 | EC1000uF/25V | C5,C16 | 04_MyFoot_Passive:CP_Radial_D10.0mm_P5.00mm
59 | EC82uF/400V | C1 | 04_MyFoot_Passive:82uF_400V

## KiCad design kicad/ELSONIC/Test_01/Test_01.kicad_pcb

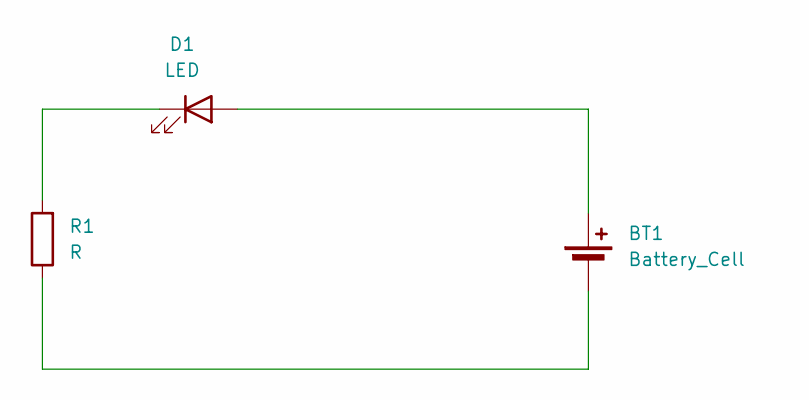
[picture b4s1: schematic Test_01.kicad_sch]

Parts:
BT1: Battery_Cell; BatteryHolder_Keystone_2466_1xAAA
D1: LED; LED_D3.0mm
R1: R; R_Axial_DIN0207_L6.3mm_D2.5mm_P10.16mm_Horizontal

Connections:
unnamed: BT1.1 (+), D1.2 (A)
unnamed: BT1.2 (-), R1.1
unnamed: D1.1 (K), R1.2
